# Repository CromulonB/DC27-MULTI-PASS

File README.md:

# DC27-MULTI-PASS
The MULTI PASS badge is running the firmware created by [badge.team](https://github.com/badgeteam/ESP32-Firmware). It is a unified badge platform that supports running apps written in python. Along with that there is a repository of apps written by other users called the [hatchery](https://badge.team/). The MULTI PASS is compatible with apps written for the SHA and HackerHotel badges.

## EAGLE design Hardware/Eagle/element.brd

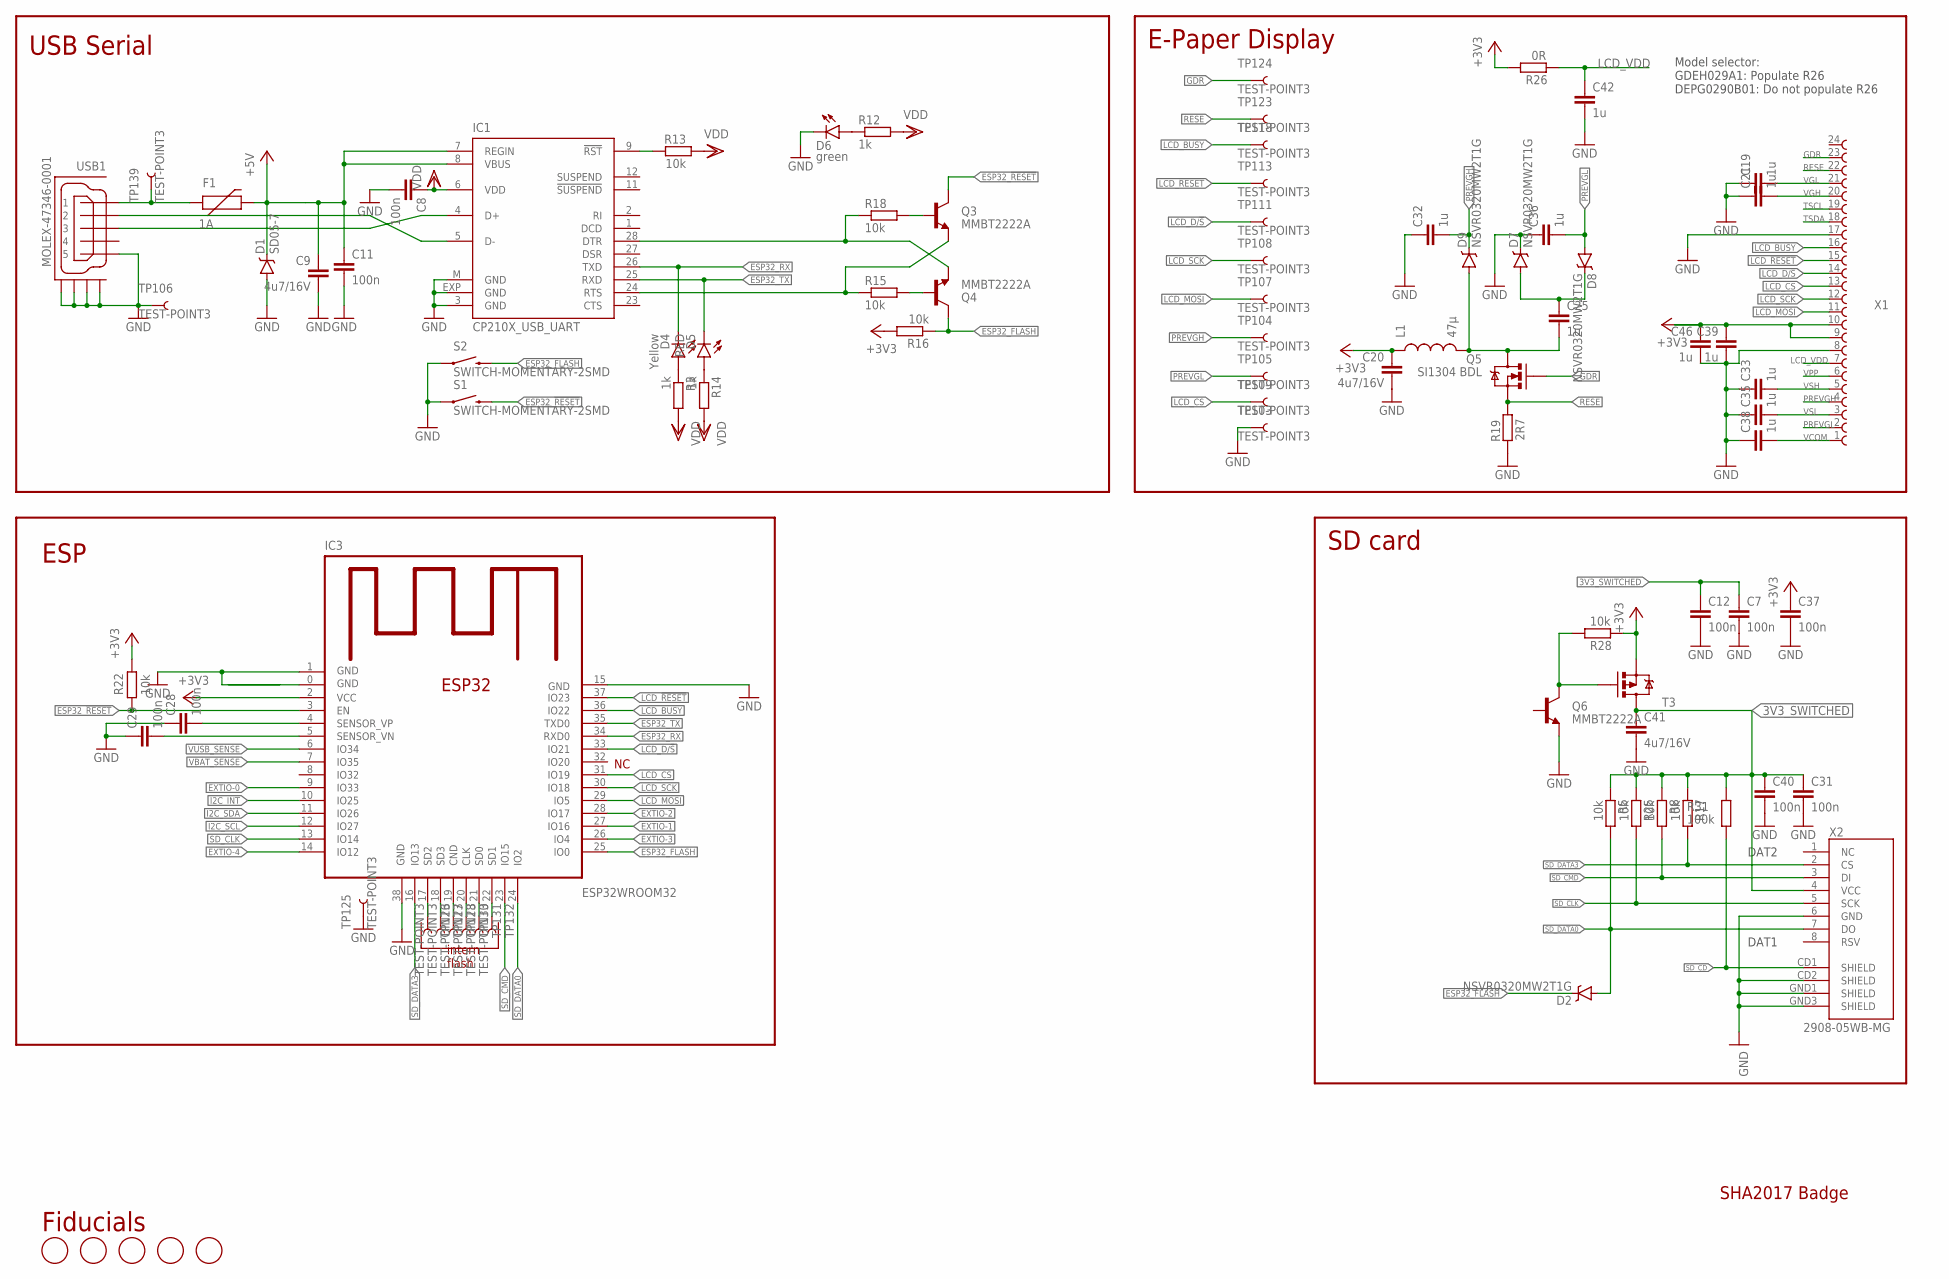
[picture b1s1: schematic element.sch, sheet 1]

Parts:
C7, C8, C11, C12, C28, C29, C31, C37, C40: 100n; C0603-DASHES; PARTNO GRM188R71H104KA93D
C9, C20, C41: 4u7/16V; C0805; PARTNO GRM21BR61C475KA88K
C19, C21, C25, C32, C33, C35, C36, C38, C39, C42, C46: 1u; C0603-DASHES; PARTNO GRM188R61E105KA12D
D1: SD05-7; SOD-323; PARTNO SD05-7
D2, D7, D8, D9: NSVR0320MW2T1G; SOD-323; PARTNO BAT20JFILM
D4: Yellow; LED-0603
D5: RED; LED-0603
D6: green; LED-0603
F1: 1A; PTC-1206
FD1, FD2, FD3, FD4, FD5: FIDUCIAL; FIDUCIAL_1MM; PARTNO NAP
IC1: CP210X_USB_UART; MLP28; PARTNO CP2102-GMR
IC3: ESP32WROOM32; ESP32MOD
L1: 47µ; 1210; PARTNO NLCV32T-220K-EF
Q3, Q4, Q6: MMBT2222A; SOT23-3; PARTNO BC817-25,215
Q5: SI1304 BDL; SOT323; PARTNO SI1308EDL-T1-GE3
R3, R12, R14: 1k; R0603-DASHES; PARTNO ERJ-3GEYJ102V
R5, R8, R13, R15, R16, R17, R18, R22, R25, R28: 10k; R0603-DASHES; PARTNO ERJ-3GEYJ103V
R19: 2R7; R0603-DASHES; PARTNO ERJ-3GEYJ5R1V
R26: 0R; R0603-DASHES; PARTNO ERJ-3GEYJ5R1V
R31: 100k; R0603-DASHES; PARTNO ERJ-3GEYJ104V
S1, S2: SWITCH-MOMENTARY-2SMD; TACTILE-SWITCH-SMD; PARTNO SKQGABE010
T3: MOSFET-PCHANNEL; SOT23-3
TP103, TP104, TP105, TP106, TP107, TP108, TP109, TP111, TP113, TP118, TP123, TP124, TP125, TP126, TP127, TP128, TP130, TP131, TP132, TP139: TEST-POINT3; PAD.03X.03; PARTNO NAP
USB1: MOLEX-47346-0001; MOLEX-47364-0001; PARTNO 10118192-0001LF
X1: 68712414022; PARTNO 68712414022
X2: 2908-05WB-MG; MICRO-SD-SOCKET-PP; PARTNO 2908-05WB-MG

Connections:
3V3_SWITCHED: C7.1, C12.1, C31.1, C40.1, C41.1, R5.2, R8.2, R17.2, R25.2, R31.1, T3.3 (D), X2.4 (VCC); also elsewhere on the board
+3V3: C20.1, C37.1, C39.1, C46.1, IC3.2 (VCC), L1.1, R16.2, R22.1, R26.1, R28.2, T3.2 (S), X1.9, X1.10; also elsewhere on the board
+5V: C9.1, C11.1, D1.C, F1.2, IC1.7 (REGIN), IC1.8 (VBUS); also elsewhere on the board
CD0: IC3.21 (SD0), TP131.P$1
CLK: IC3.20 (CLK), TP130.P$1
CND: IC3.19 (CND), TP128.P$1
ESP32_!RESET: IC3.3 (EN), Q3.3 (C), R22.2, S1.3 (2); also elsewhere on the board
ESP32_FLASH: D2.C, IC3.25 (IO0), Q4.3 (C), R16.1, S2.3 (2); also elsewhere on the board
ESP32_RX: D4.C, IC1.26 (TXD), IC3.34 (RXD0); also elsewhere on the board
ESP32_TX: D5.C, IC1.25 (RXD), IC3.35 (TXD0); also elsewhere on the board
EXTIO-0: IC3.9 (IO33); also elsewhere on the board
EXTIO-1: IC3.27 (IO16); also elsewhere on the board
EXTIO-2: IC3.28 (IO17); also elsewhere on the board
EXTIO-3: IC3.26 (IO4); also elsewhere on the board
EXTIO-4: IC3.14 (IO12); also elsewhere on the board
GDR: Q5.1 (G), TP124.P$1, X1.23
GND: C7.2, C8.2, C9.2, C11.2, C12.2, C19.1, C20.2, C21.1, C28.1, C29.1, C31.2, C32.1, C33.1, C35.1, C36.1, C37.2, C38.1, C39.2, C40.2, C41.2, C42.2, C46.2, D1.A, D6.C, D7.C, IC1.3 (GND), IC1.EXP (GND), IC1.M (GND), IC3.0 (GND), IC3.1 (GND), IC3.15 (GND), IC3.38 (GND), Q6.2 (E), R19.2, S1.1, S2.1, TP103.P$1, TP106.P$1, TP125.P$1, USB1.5, USB1.GND1, USB1.GND2, USB1.GND3, USB1.GND4, X1.8, X1.17, X2.6 (GND), X2.CD2 (SHIELD), X2.GND1 (SHIELD), X2.GND3 (SHIELD); also elsewhere on the board
I2C_INT: IC3.10 (IO25); also elsewhere on the board
I2C_SCL: IC3.12 (IO27); also elsewhere on the board
I2C_SDA: IC3.11 (IO26); also elsewhere on the board
LCD_!RESET: IC3.37 (IO23), TP113.P$1, X1.15
LCD_BUSY: IC3.36 (IO22), TP118.P$1, X1.16
LCD_CS: IC3.31 (IO19), TP109.P$1, X1.13
LCD_D/!S: IC3.33 (IO21), TP111.P$1, X1.14
LCD_MOSI: IC3.29 (IO5), TP107.P$1, X1.11
LCD_SCK: IC3.30 (IO18), TP108.P$1, X1.12
LCD_VDD: C42.1, R26.2, X1.7
unnamed: IC1.9 (!RST), R13.2
unnamed: IC1.24 (RTS), Q3.2 (E), R15.1
unnamed: IC1.28 (DTR), Q4.2 (E), R18.1
unnamed: Q4.1 (B), R15.2
unnamed: Q3.1 (B), R18.2
unnamed: Q6.3 (C), R28.1, T3.1 (G)
unnamed: C25.1, D7.A, D8.C
unnamed: C25.2, D9.A, L1.2, Q5.3 (D)
unnamed: D6.A, R12.1
unnamed: D4.A, R3.1
unnamed: D5.A, R14.1
unnamed: F1.1, TP139.P$1, USB1.1
unnamed: C28.2, IC3.4 (SENSOR_VP)
unnamed: C29.2, IC3.5 (SENSOR_VN)
PREVGH: C32.2, D9.C, TP104.P$1, X1.4
PREVGL: C36.2, D8.A, TP105.P$1, X1.2
RESE: Q5.2 (S), R19.1, TP123.P$1, X1.22
SD1: IC3.22 (SD1), TP132.P$1
SD2: IC3.17 (SD2), TP126.P$1
SD3: IC3.18 (SD3), TP127.P$1
SD_CD: R31.2, X2.CD1 (SHIELD); also elsewhere on the board
SD_CLK: IC3.13 (IO14), R25.1, X2.5 (SCK)
SD_CMD: IC3.23 (IO15), R8.1, X2.3 (DI)
SD_DATA0: D2.A, IC3.24 (IO2), R5.1, X2.7 (DO)
SD_DATA3: IC3.16 (IO13), R17.1, X2.2 (CS)
TSCL: X1.19
TSDA: X1.18
USB_DN_CON: IC1.5 (D-), USB1.2; also elsewhere on the board
USB_DP_CON: IC1.4 (D+), USB1.3; also elsewhere on the board
VBAT_SENSE: IC3.7 (IO35); also elsewhere on the board
VCOM: C38.2, X1.1
VDD: C8.1, IC1.6 (VDD), R3.2, R12.2, R13.1, R14.2
VGH: C21.2, X1.20
VGL: C19.2, X1.21
VPP: X1.6
VSH: C33.2, X1.5
VSL: C35.2, X1.3
VUSB_SENSE: IC3.6 (IO34); also elsewhere on the board

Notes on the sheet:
USB Serial
E-Paper Display
SD card
intern flash
ESP
Fiducials
DAT1
DAT2
Model selector: GDEH029A1: Populate R26 DEPG0290B01: Do not populate R26
SHA2017 Badge

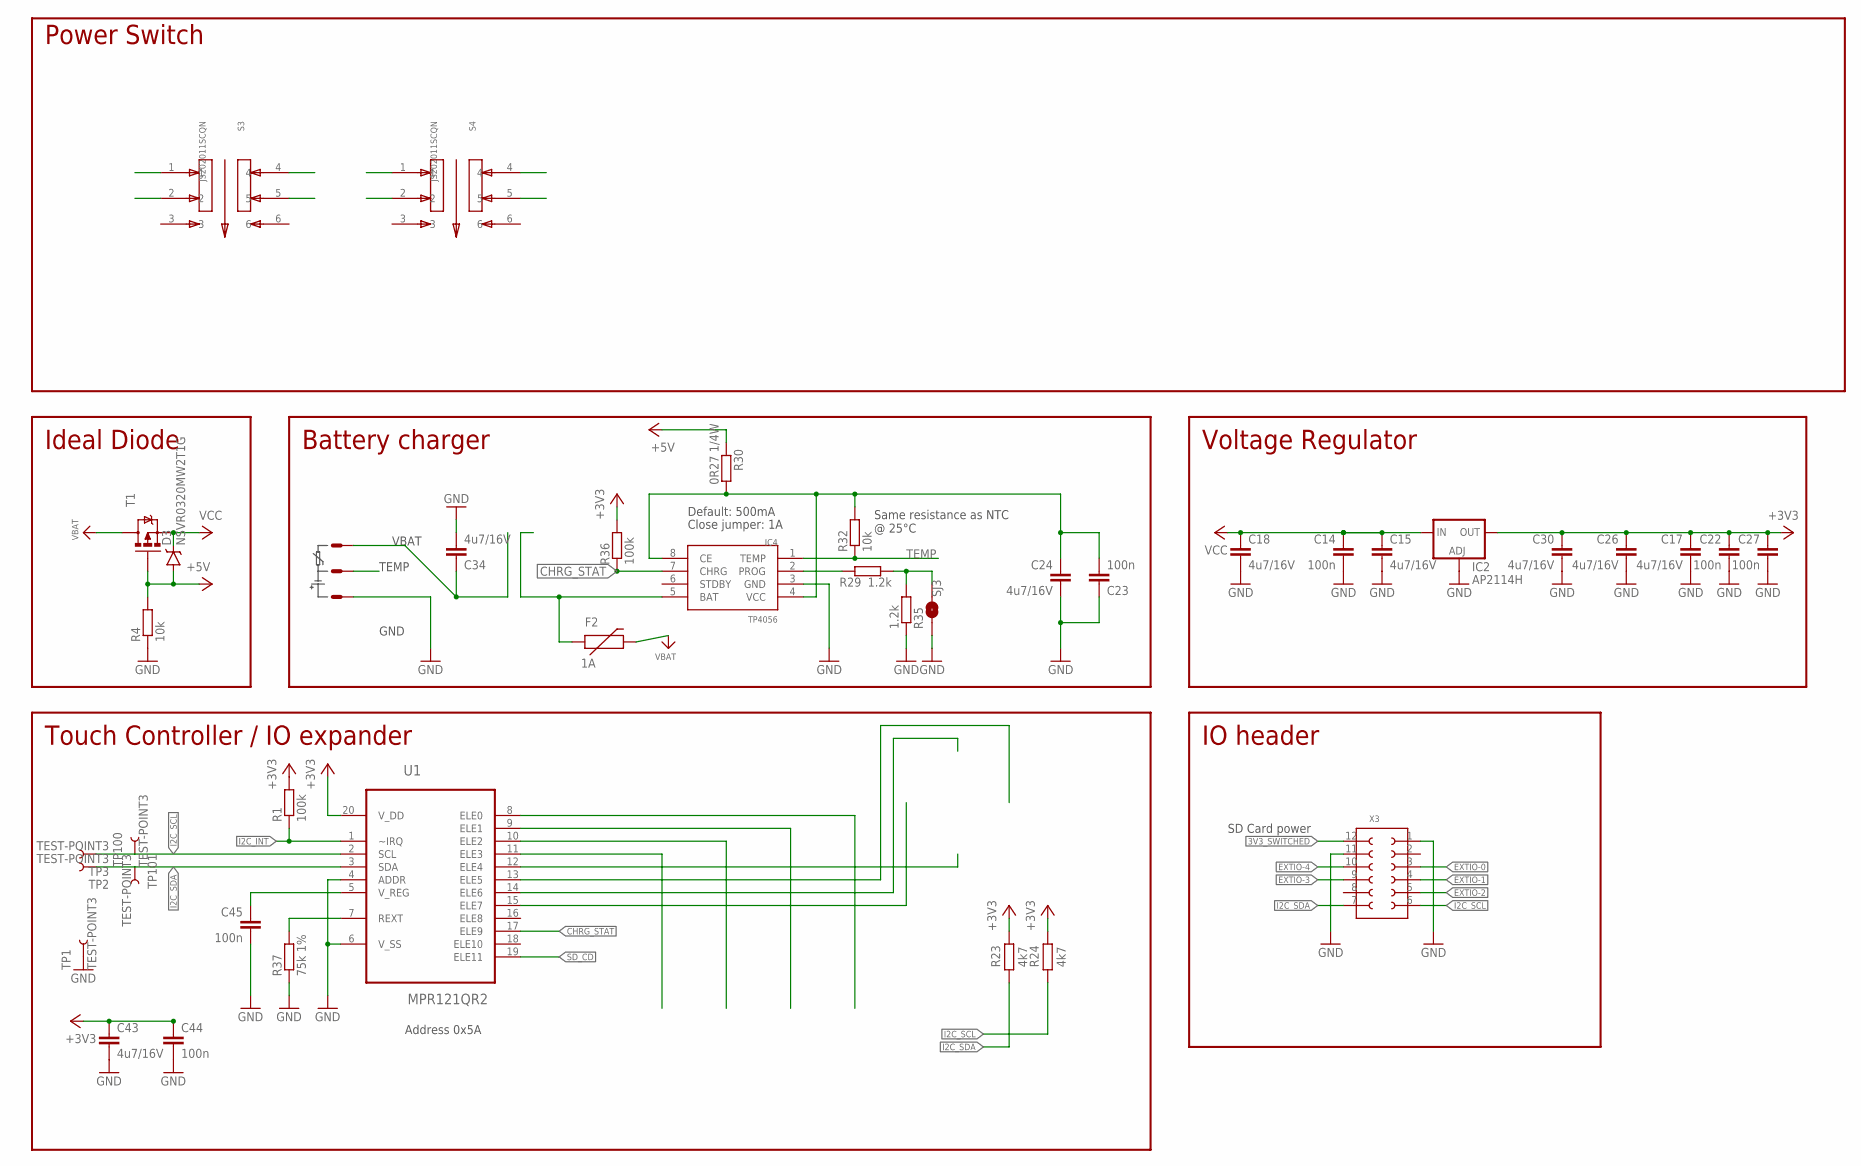
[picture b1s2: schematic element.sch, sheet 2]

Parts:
C14, C22, C23, C27, C44, C45: 100n; C0603-DASHES; PARTNO GRM188R71H104KA93D
C15, C17, C18, C24, C26, C30, C34, C43: 4u7/16V; C0805; PARTNO GRM21BR61C475KA88K
D3: NSVR0320MW2T1G; SOD-323; PARTNO BAT20JFILM
F2: 1A; PTC-1206
IC2: AP2114H; SOT223; PARTNO AP7215-33YG-13
IC4: TP4056; SOP-8
R1, R36: 100k; R0603-DASHES; PARTNO ERJ-3GEYJ104V
R4: 10k; R0603-DASHES; PARTNO ERJ-3GEYJ103V
R23, R24: 4k7; R0603-DASHES; PARTNO ERJ-3GEYJ103V
R29, R35: 1.2k; R0603-DASHES; PARTNO ERJ-3GEYJ222V
R30: 0R27 1/4W; R1206; PARTNO ERJ-3GEYJ154V
R32: 10k; R0603-DASHES; PARTNO ERJ-3GEYJ154V
R37: 75k 1%; R0603-DASHES; PARTNO ERJ-3GEYJ104V
S3, S4: JS202011SCQN; SW_JS202011SCQN
SJ3: JUMPER-PAD-2-NOYES_SILK; PAD-JUMPER-2-NO_YES_SILK; PARTNO NAP
T1: MOSFET-PCHANNEL; SOT23-3
TP1, TP2, TP3, TP100, TP101: TEST-POINT3; PAD.03X.03; PARTNO NAP
U1: MPR121QR2; QFN40P300X300X60-20N
X3: 610X12243021; PARTNO 517-153208-2020-TB
X4: JST-PH3

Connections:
3V3_SWITCHED: X3.12 (1); also elsewhere on the board
+3V3: C17.1, C22.1, C26.1, C27.1, C30.1, C43.1, C44.1, IC2.4 (OUT), R1.2, R23.1, R24.1, R36.2, U1.20 (V_DD); also elsewhere on the board
+5V: D3.A, R4.2, R30.1, T1.1 (G); also elsewhere on the board
BLPWR: S4.1, S4.4; also elsewhere on the board
CHRG_STAT: IC4.7 (CHRG), R36.1, U1.17 (ELE9)
EXTIO-0: X3.3 (10); also elsewhere on the board
EXTIO-1: X3.4 (9); also elsewhere on the board
EXTIO-2: X3.5 (8); also elsewhere on the board
EXTIO-3: X3.9 (4); also elsewhere on the board
EXTIO-4: X3.10 (3); also elsewhere on the board
GND: C14.2, C15.2, C17.2, C18.2, C22.2, C23.1, C24.2, C26.2, C27.2, C30.2, C34.2, C43.2, C44.2, C45.2, IC2.1 (ADJ), IC4.3 (GND), R4.1, R35.2, R37.1, SJ3.1, TP1.P$1, U1.4 (ADDR), U1.6 (V_SS), X3.1 (12), X3.11 (2), X4.3; also elsewhere on the board
I2C_INT: R1.1, U1.1 (~IRQ); also elsewhere on the board
I2C_SCL: R24.2, TP3.P$1, TP100.P$1, U1.2 (SCL), X3.6 (7); also elsewhere on the board
I2C_SDA: R23.2, TP2.P$1, TP101.P$1, U1.3 (SDA), X3.7 (6); also elsewhere on the board
unnamed: IC4.2 (PROG), R29.1
unnamed: R29.2, R35.1, SJ3.2
unnamed: C23.2, C24.1, IC4.4 (VCC), IC4.8 (CE), R30.2, R32.2
unnamed: C45.1, U1.5 (V_REG)
unnamed: R37.2, U1.7 (REXT)
unnamed: F2.1, IC4.5 (BAT), S3.1, S3.4
SD_CD: U1.19 (ELE11); also elsewhere on the board
SWBDG: C34.1, S3.2, S3.5, S4.2, S4.5, X4.1
TEMP: IC4.1 (TEMP), R32.1, X4.2
VBAT: F2.2, T1.3 (D); also elsewhere on the board
VCC: C14.1, C15.1, C18.1, D3.C, IC2.3 (IN), T1.2 (S); also elsewhere on the board

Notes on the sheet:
Voltage Regulator
Battery charger
Ideal Diode
Default: 500mA
Close jumper: 1A
GND
VBAT
Same resistance as NTC @ 25°C
Touch Controller / IO expander
Address 0x5A
IO header
SD Card power
Power Switch
TEMP

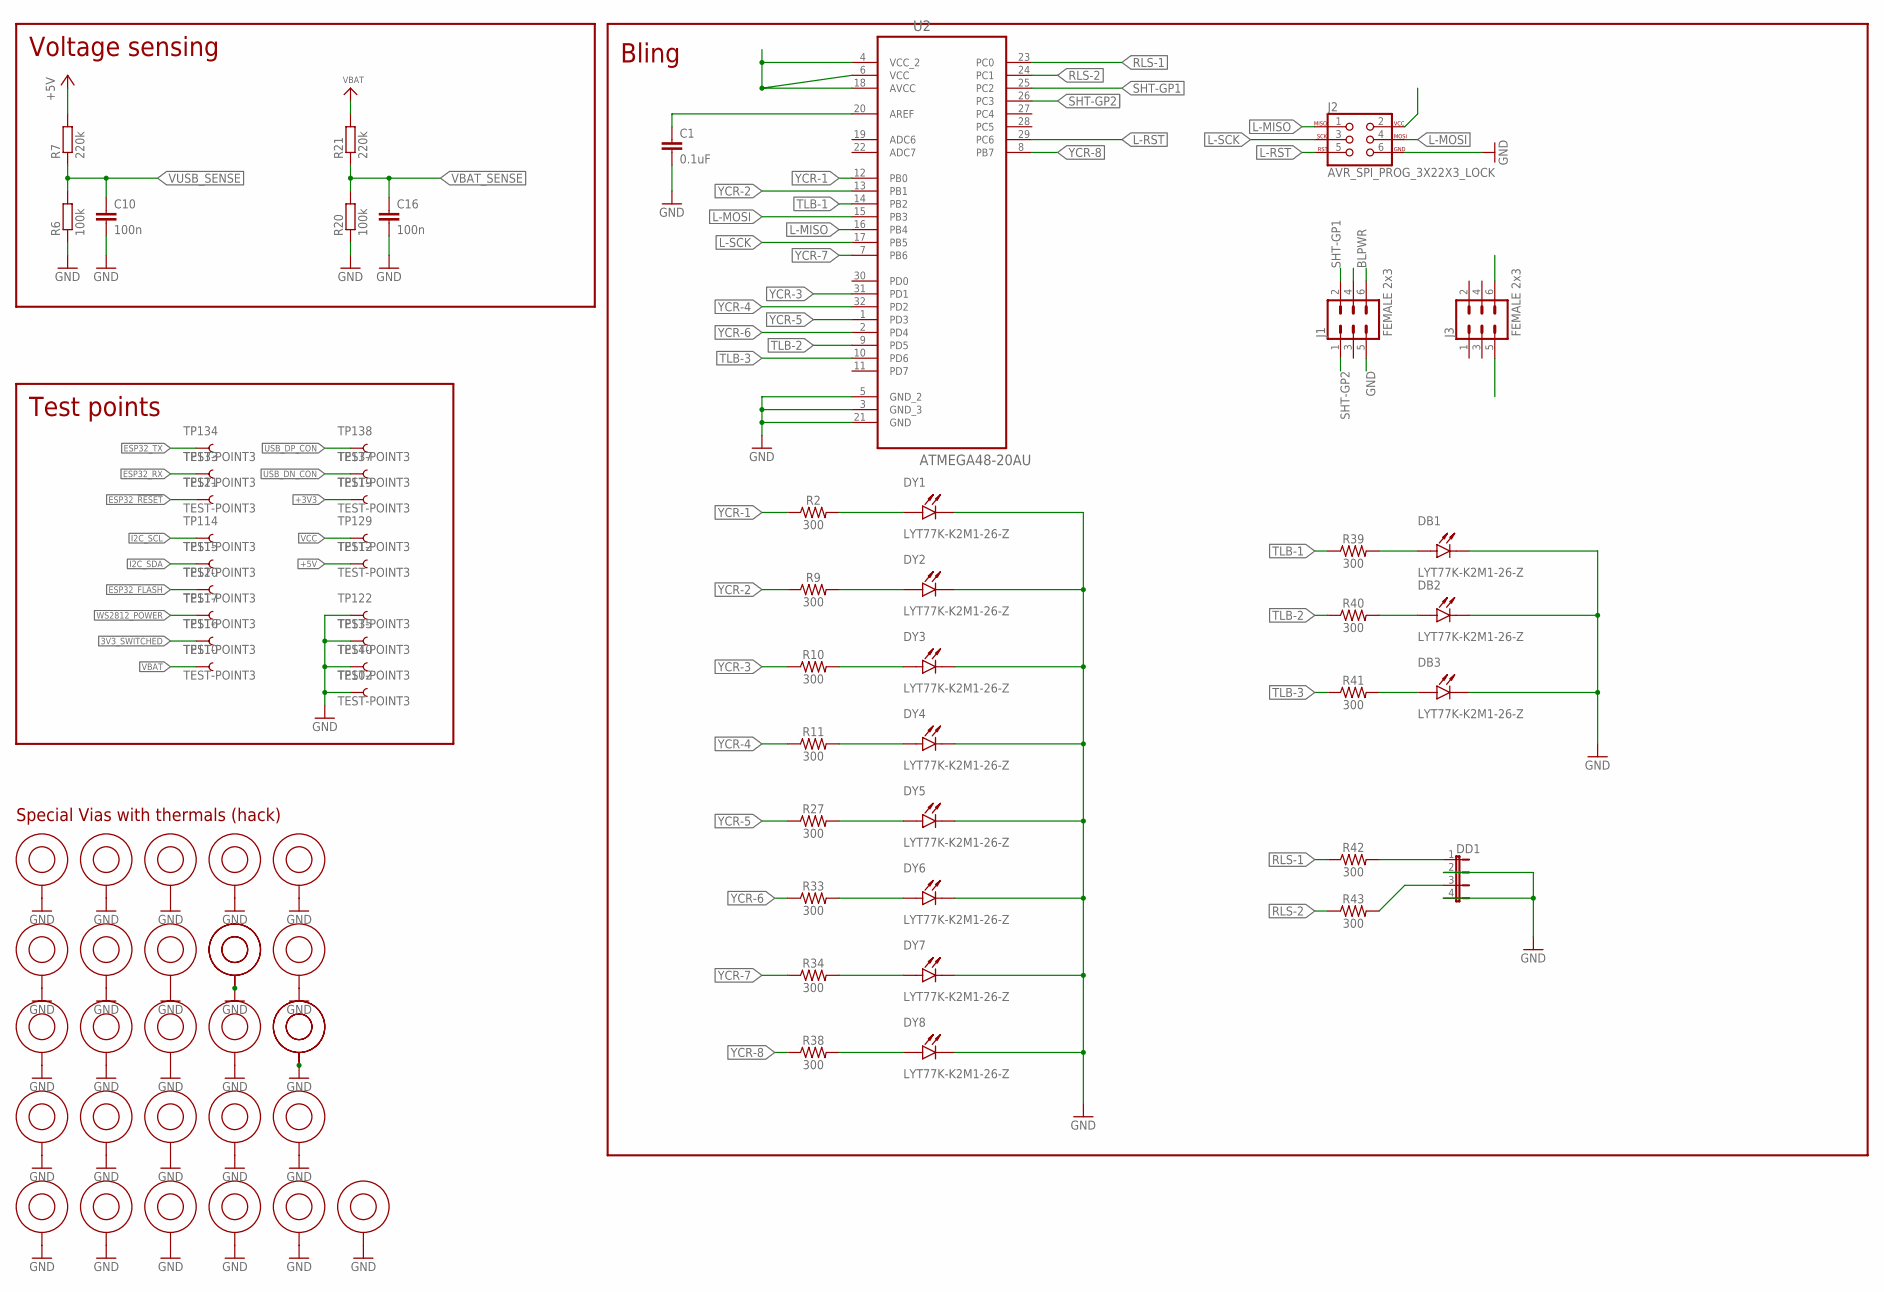
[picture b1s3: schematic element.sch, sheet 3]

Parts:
$$U$1, $$U$2, $$U$3, $$U$4, $$U$5, $$U$6, $$U$7, $$U$8, $$U$9: VIA; PARTNO NAP
C1: 0.1uF; 0603
C10, C16: 100n; C0603-DASHES; PARTNO GRM188R71H104KA93D
DB1, DB2, DB3: LYT77K-K2M1-26-Z; LED_LYT77K-K2M1-26-Z
DD1: JP4E; JP4
DY1, DY2, DY3, DY4, DY5, DY6, DY7, DY8: LYT77K-K2M1-26-Z; LED_LYT77K-K2M1-26-Z
J1, J3: FEMALE 2x3; 2X3
J2: AVR_SPI_PROG_3X22X3_LOCK; 2X3_LOCK
R2, R9, R10, R11, R27, R33, R34, R38, R39, R40, R41, R42, R43: 300; 0603
R6, R20: 100k; R0603-DASHES; PARTNO ERJ-3GEYJ104V
R7, R21: 220k; R0603-DASHES; PARTNO ERJ-3GEYJ224V
TP102, TP110, TP112, TP114, TP115, TP116, TP117, TP119, TP120, TP121, TP122, TP129, TP133, TP134, TP135, TP137, TP138, TP140: TEST-POINT3; PAD.03X.03; PARTNO NAP
U2: ATMEGA48-20AU; QFP80P900X900X120-32N
U$2, U$3, U$4, U$5, U$6, U$10, U$11, U$12, U$13, U$14, U$15, U$16, U$17, U$18, U$19, U$20, U$21, U$22, U$23: VIA; PARTNO NAP

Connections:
3V3_SWITCHED: TP116.P$1; also elsewhere on the board
+3V3: TP119.P$1; also elsewhere on the board
+5V: R7.2, TP112.P$1; also elsewhere on the board
BLPWR: J1.6, J2.2, J3.6, U2.4 (VCC_2), U2.6 (VCC), U2.18 (AVCC); also elsewhere on the board
ESP32_!RESET: TP121.P$1; also elsewhere on the board
ESP32_FLASH: TP120.P$1; also elsewhere on the board
ESP32_RX: TP133.P$1; also elsewhere on the board
ESP32_TX: TP134.P$1; also elsewhere on the board
GND: $$U$1.P$1, $$U$2.P$1, $$U$3.P$1, $$U$4.P$1, $$U$5.P$1, $$U$6.P$1, $$U$7.P$1, $$U$8.P$1, $$U$9.P$1, C1.2, C10.2, C16.2, DB1.1 (C), DB2.1 (C), DB3.1 (C), DD1.2, DD1.4, DY1.1 (C), DY2.1 (C), DY3.1 (C), DY4.1 (C), DY5.1 (C), DY6.1 (C), DY7.1 (C), DY8.1 (C), J1.5, J2.6, J3.5, R6.1, R20.1, TP102.P$1, TP122.P$1, TP135.P$1, TP140.P$1, U2.3 (GND_3), U2.5 (GND_2), U2.21 (GND), U$2.P$1, U$3.P$1, U$4.P$1, U$5.P$1, U$6.P$1, U$10.P$1, U$11.P$1, U$12.P$1, U$13.P$1, U$14.P$1, U$15.P$1, U$16.P$1, U$17.P$1, U$18.P$1, U$19.P$1, U$20.P$1, U$21.P$1, U$22.P$1, U$23.P$1; also elsewhere on the board
I2C_SCL: TP114.P$1; also elsewhere on the board
I2C_SDA: TP115.P$1; also elsewhere on the board
L-MISO: J2.1, U2.16 (PB4)
L-MOSI: J2.4, U2.15 (PB3)
L-RST: J2.5, U2.29 (PC6)
L-SCK: J2.3, U2.17 (PB5)
unnamed: DY1.2 (A), R2.2
unnamed: DY2.2 (A), R9.2
unnamed: DY3.2 (A), R10.2
unnamed: DY4.2 (A), R11.2
unnamed: DY5.2 (A), R27.2
unnamed: DY6.2 (A), R33.2
unnamed: DY7.2 (A), R34.2
unnamed: DY8.2 (A), R38.2
unnamed: DD1.1, R42.2
unnamed: DD1.3, R43.2
unnamed: DB1.2 (A), R39.2
unnamed: DB2.2 (A), R40.2
unnamed: DB3.2 (A), R41.2
unnamed: C1.1, U2.20 (AREF)
RLS-1: R42.1, U2.23 (PC0)
RLS-2: R43.1, U2.24 (PC1)
SHT-GP1: J1.2, U2.25 (PC2)
SHT-GP2: J1.1, U2.26 (PC3)
TLB-1: R39.1, U2.14 (PB2)
TLB-2: R40.1, U2.9 (PD5)
TLB-3: R41.1, U2.10 (PD6)
USB_DN_CON: TP137.P$1; also elsewhere on the board
USB_DP_CON: TP138.P$1; also elsewhere on the board
VBAT: R21.2, TP110.P$1; also elsewhere on the board
VBAT_SENSE: C16.1, R20.2, R21.1; also elsewhere on the board
VCC: TP129.P$1; also elsewhere on the board
VUSB_SENSE: C10.1, R6.2, R7.1; also elsewhere on the board
WS2812_POWER: TP117.P$1
YCR-1: R2.1, U2.12 (PB0)
YCR-2: R9.1, U2.13 (PB1)
YCR-3: R10.1, U2.31 (PD1)
YCR-4: R11.1, U2.32 (PD2)
YCR-5: R27.1, U2.1 (PD3)
YCR-6: R33.1, U2.2 (PD4)
YCR-7: R34.1, U2.7 (PB6)
YCR-8: R38.1, U2.8 (PB7)

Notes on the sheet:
Special Vias with thermals (hack)
Test points
Voltage sensing
Bling

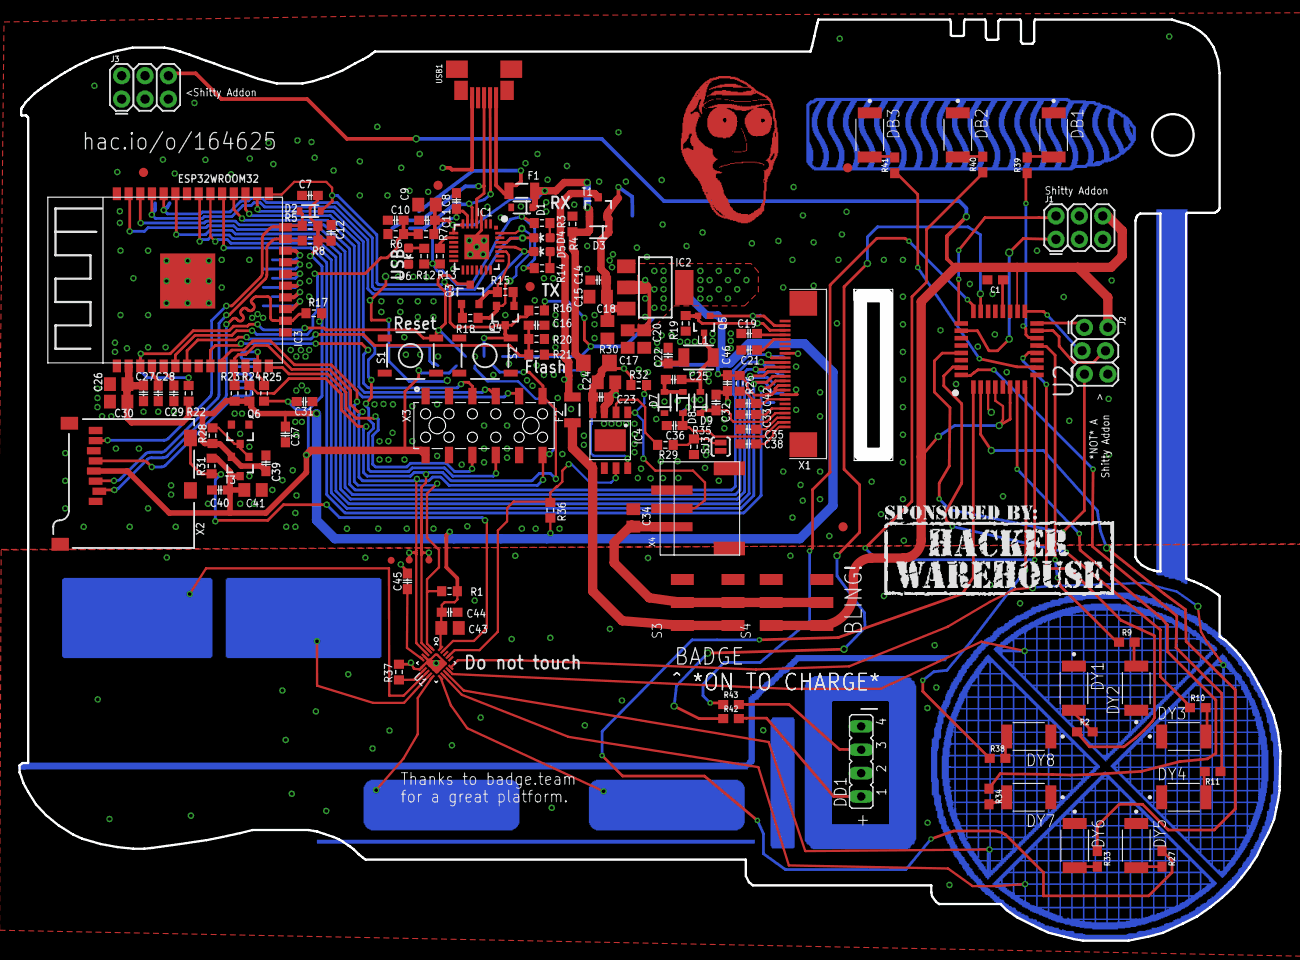
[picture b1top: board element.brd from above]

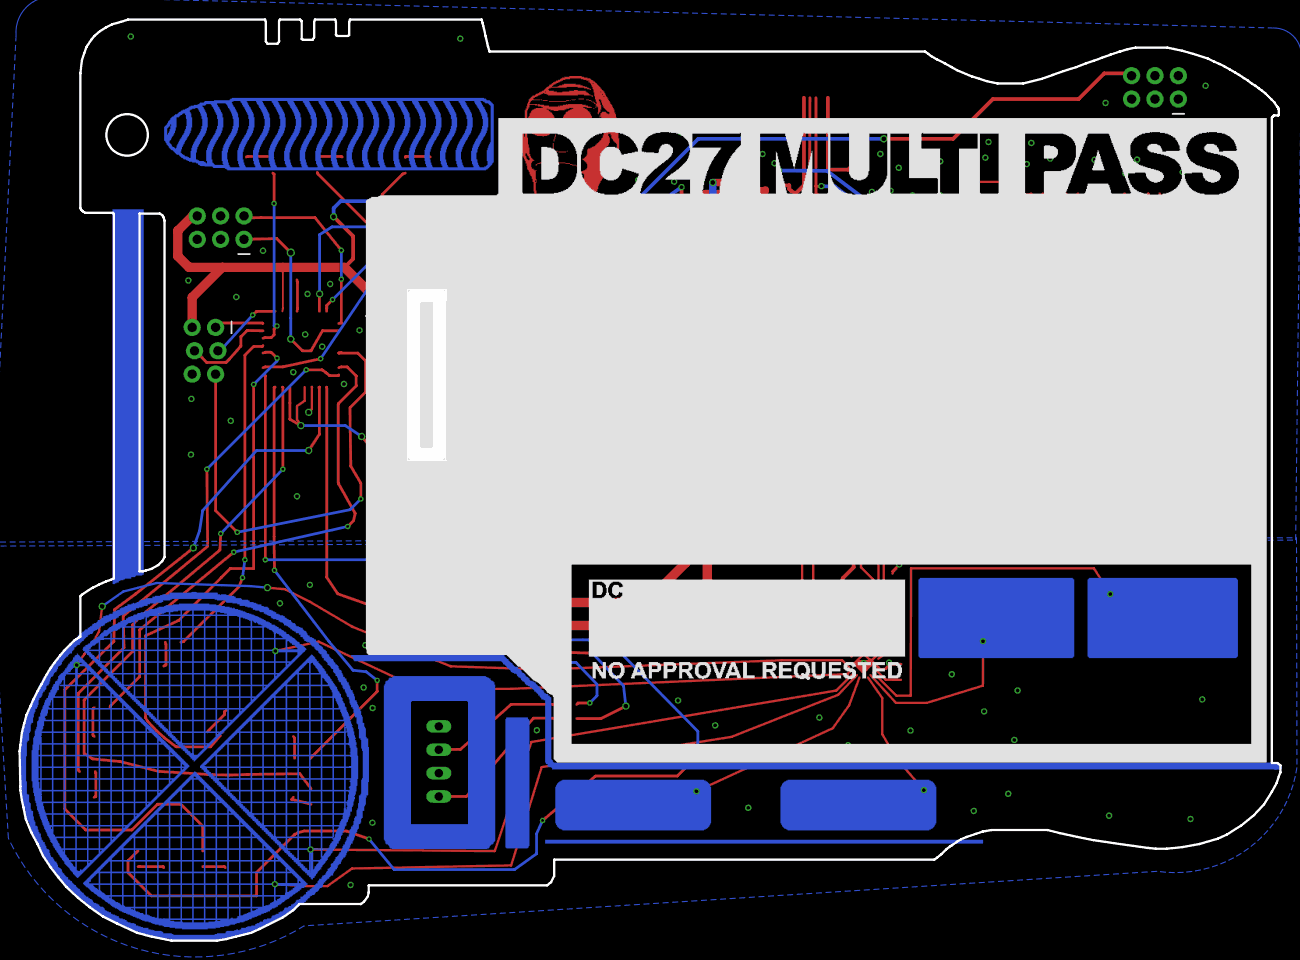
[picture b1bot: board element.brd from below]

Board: 2 copper layers, 137.0 x 100.1 mm, 208 parts (40 on the bottom side), 107 nets.

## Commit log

2019-07-28 Create Software
2019-08-05 Hardware Updates
2019-09-06 Firmware Update 2

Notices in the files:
parts and their libraries:
SparkFun-DigitalIC: Licensing: Creative Commons ShareAlike 4.0 International - https://creativecommons.org/licenses/by-sa/4.0
EAGLE-FPC_CONNECTOR_AND_FFC_CAB-rev1: Copyright: Würth Elektronik
